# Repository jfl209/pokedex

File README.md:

# Pokédex

A software revival of the 1999 Tiger Electronics Pokémon Pokédex, running on a Raspberry Pi Zero 2 W with a 240×240 Adafruit TFT (ST7789) replacing the original LCD.

| | | |
|---|---|---|
|  |  |  |
| Original device (front) | Inside — keyboard + LiPo | Original PCB removed |

## Hardware

| Component | Part |
|-----------|------|
| Shell | Tiger Electronics Pokédex (1999) |
| SBC | Raspberry Pi Zero 1.1 W / Zero 2 W |
| Display | Adafruit 1.3" 240×240 TFT (ST7789, SPI) |
| Keyboard | Original PCB re-routed through custom PCB; scanned by ATtiny1614 over USB HID |
| Audio | Original speaker wired to Pi audio output |

### Custom PCB

The [`hardware/`](hardware/) directory contains the KiCad schematic and PCB layout for the interface board that sits between the Pi and the original Pokédex keyboard membrane.

| File | Description |
|------|-------------|
| `pi-zero-mainboard.kicad_sch` | Schematic |
| `pi-zero-mainboard.kicad_pcb` | PCB layout |
| `pi-zero-mainboard.kicad_pro` | KiCad project file |

## Software architecture

```
main.py                 Entry point — game loop
config.py               Constants: resolution, scale factor, palette, paths

data/
  fetch.py              One-time setup: pulls Gen-1 data from PokéAPI → SQLite + assets
  db.py                 SQLite query layer (Pokemon dataclass, get_all/get_by_id/search)

engine/
  display.py            Pygame surface abstraction (scaled window on dev, /dev/fb0 on Pi)
  input.py              Keyboard → Button enum (UP/DOWN/A/B/START/SELECT)
  sound.py              Pokémon cry playback via pygame.mixer

screens/
  base.py               Screen ABC: update(state) → Screen | None, draw(surface)
  home.py               Title / splash screen
  browse.py             Scrollable list of all 151 Pokémon
  detail.py             3-page detail view: info · stats · description
```

The display runs natively at 240×240. On a development machine it auto-scales 3× (720×720 window) so you can work without the physical hardware.

## Setup

### Dependencies

Requires Python 3.11–3.13 (pygame has no wheel for 3.14 yet).

```bash
python3.13 -m venv .venv
source .venv/bin/activate
pip install -r requirements.txt
```

### Fetch Pokémon data

Downloads sprites, cries, and stats for all 151 Gen-1 Pokémon from [PokéAPI](https://pokeapi.co). Takes ~10 minutes (rate-limited out of courtesy to the free API).

```bash
python -m data.fetch
```

### Run (development — Mac/Linux desktop)

```bash
python main.py
```

### Run (Raspberry Pi)

Install Pi-specific dependencies once:

```bash
sudo apt install python3-numpy python3-evdev -y
pip install spidev RPi.GPIO
```

Enable SPI in `/boot/firmware/config.txt` (Bookworm) or `/boot/config.txt` (Bullseye):

```ini
dtparam=spi=on
```

Then launch:

```bash
python3 main.py
```

The display driver auto-detects: ST7789 direct SPI → kmsdrm (HDMI) → offscreen.
FPS is auto-tuned: 20fps on Pi Zero 1.1 W (armv6l), 30fps everywhere else.

## Controls

| Physical key | Dev key | Action |
|---|---|---|
| D-pad up/down | `↑` `↓` | Navigate list; prev/next Pokémon in detail |
| D-pad left/right | `←` `→` | Flip detail pages |
| A | `Enter` or `Z` | Select / next page |
| B | `Backspace` or `X` | Back |
| START | `Escape` | Return to home |

## Detail pages

Each Pokémon detail view has three swipeable pages:

1. **Info** — sprite, type badges, category, height, weight
2. **Stats** — HP / ATK / DEF / SPD / SPA / SPD bars (colour-coded)
3. **Description** — original Red/Blue Pokédex flavour text

## Project status

- [x] Core game loop (display, input, sound abstractions)
- [x] PokéAPI data fetch + SQLite storage
- [x] Home, browse, and detail screens
- [ ] Search / filter screen
- [ ] Quiz mode (silhouette / cry identification)
- [ ] Battle simulation
- [ ] ATtiny1614 firmware (keyboard scanner)
- [ ] Pi OS image + auto-start service

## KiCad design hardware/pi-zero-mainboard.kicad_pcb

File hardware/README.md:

# Pi Zero 2 W Mainboard — KiCad Project

## Overview

Custom PCB that the Pi Zero 2 W plugs into via GPIO header. Integrates:
- USB-C charging (MCP73871 power-path manager)
- 3.7V→5.2V boost (TPS61090)
- Soft-latch power control via TPS61090 EN pin
- 1.54" 240×240 TFT display connector (ST7789, SPI)
- MAX98357A I2S DAC + Class D amp with speaker connector
- ATtiny1614 keyboard controller (on-board, SOIC-14)
- 48 switches + 48 diodes (charlieplex matrix, directly on PCB)

Board dimensions: 76 × 114 mm (3" × 4.5"), 2-layer, 1.6mm thickness.

## Power Architecture

Based on the **Adafruit PowerBoost 1000C** (open-source hardware).
Copy the MCP73871 and TPS61090 subcircuits with all component values
from the PowerBoost 1000C schematic (Eagle files on GitHub).

### Changes from PowerBoost 1000C

| What | PowerBoost 1000C | This board |
|------|-----------------|------------|
| USB input | Micro-USB | USB-C with 5.1kΩ CC pulldowns |
| USB output | USB-A jack + iOS resistors | Removed (not needed) |
| Power LED | Blue LED on 5V output | Removed (saves ~5mA) |
| EN pin | Pulled high to VS (always on) | Driven by POWER_CTRL net (soft-latch) |
| Low battery | Red LED on LBO | Keep LED, optionally route to Pi GPIO |

### Soft-Latch Power Control

No P-FET or external latch circuit needed! The TPS61090's EN pin does it all:

- R5 (100kΩ) pulls EN to GND → boost OFF by default
- ATtiny1614 PB3 drives POWER_CTRL HIGH → boost ON (Pi boots)
- Pi GPIO 26 also drives POWER_CTRL HIGH (wired-OR with ATtiny)
- Pi shutdown releases GPIO 26, ATtiny releases PB3 → EN goes LOW → power off
- Quiescent draw in off state: ~20µA (TPS61090 disabled)

### ATtiny1614 Always-On Power

The ATtiny1614 (on the keyboard PCB) connects directly to VLIPO (raw battery)
through J1 pin 1. It draws ~1µA in power-down sleep mode, waking on
pin-change interrupt when the ON key is pressed.

## Net Names

| Net | Description | Source |
|-----|-------------|--------|
| VBUS | USB-C 5V input | J6 USB-C connector |
| VLIPO | Raw battery (3.0–4.2V) | J2 LiPo JST connector |
| VBAT_OUT | MCP73871 OUT (load-shared) | U1 pin 19 |
| 5V_BOOST | TPS61090 output (5.2V) | U2 pin 1 → Pi pin 2 |
| POWER_CTRL | Soft-latch enable | ATtiny PB3 + Pi GPIO 26 → U2 EN |
| +3V3 | Pi 3.3V rail (from Pi's regulator) | Pi pin 1 |
| SDA | I2C data | Pi GPIO 2 (pin 3) ↔ ATtiny PA1 |
| SCL | I2C clock | Pi GPIO 3 (pin 5) ↔ ATtiny PA2 |

## GPIO Assignment (Pi Zero 2 W)

| GPIO | Pin | Function | Peripheral |
|------|-----|----------|-----------|
| 2 | 3 | I2C SDA | Keyboard (ATtiny1614) |
| 3 | 5 | I2C SCL | Keyboard (ATtiny1614) |
| 4 | 7 | SD_MODE | MAX98357A shutdown |
| 8 | 24 | SPI0 CE0 | Display TFT CS |
| 10 | 19 | SPI0 MOSI | Display data |
| 11 | 23 | SPI0 SCLK | Display clock |
| 18 | 12 | I2S BCLK | MAX98357A bit clock |
| 19 | 35 | I2S LRCLK | MAX98357A word clock |
| 21 | 40 | I2S DIN | MAX98357A data in |
| 25 | 22 | DC | Display data/command |
| 26 | 37 | KEEP_ALIVE | POWER_CTRL (soft-latch) |

## Connector Pinouts

### J1 — Keyboard (5-pin, to keyboard PCB)
| Pin | Signal | Notes |
|-----|--------|-------|
| 1 | VLIPO | ATtiny always-on power (3.0–4.2V) |
| 2 | SDA | I2C data (Pi has 1.8kΩ pull-up) |
| 3 | SCL | I2C clock (Pi has 1.8kΩ pull-up) |
| 4 | GND | Ground |
| 5 | POWER_CTRL | ATtiny PB3 output to TPS61090 EN |

### J2 — LiPo Battery (JST-PH 2-pin)
| Pin | Signal |
|-----|--------|
| 1 | VLIPO (+) |
| 2 | GND (−) |

### J4 — Display (7-pin header)
| Pin | Signal | Pi GPIO |
|-----|--------|---------|
| 1 | 3.3V | Pin 1 |
| 2 | GND | Pin 6 |
| 3 | SPI_SCLK | GPIO 11 |
| 4 | SPI_MOSI | GPIO 10 |
| 5 | SPI_CE0 | GPIO 8 |
| 6 | DC | GPIO 25 |
| 7 | RST | GPIO 24 (or tie to 3.3V via RC) |

### J5 — Speaker (JST-PH 2-pin)
| Pin | Signal |
|-----|--------|
| 1 | OUTP |
| 2 | OUTN |

## BOM (Key Components)

| Ref | Part | Package | Value/Part # | Notes |
|-----|------|---------|-------------|-------|
| U1 | MCP73871-2CCI/ML | QFN-20 4×4mm | — | Copy from PowerBoost |
| U2 | TPS61090RSAR | PVQFN-16 | — | Copy from PowerBoost |
| U3 | MAX98357AETE | TQFN-16 3×3mm | — | I2S DAC + amp |
| J6 | USB-C receptacle | GCT USB4085 | — | Mid-mount |
| J3 | 2×20 female header | 2.54mm pitch | — | For Pi Zero GPIO |
| J1 | 1×5 pin header | 2.54mm pitch | — | Keyboard cable |
| J2 | JST-PH 2-pin | S2B-PH-K | — | LiPo battery |
| J4 | 1×7 pin header | 2.54mm pitch | — | Display module |
| J5 | JST-PH 2-pin | S2B-PH-K | — | Speaker |
| L1 | Inductor | 5×5mm | 6.8µH | TDK VLC5045 or similar |
| R1,R2 | Resistor | 0402 | 5.1kΩ | USB-C CC pulldowns |
| R5 | Resistor | 0402 | 100kΩ | EN pull-down (soft-latch) |
| — | (PowerBoost passives) | 0402/0805 | Various | Copy values from PB1000C |

## Getting Started

1. Open `pi-zero-mainboard.kicad_pro` in KiCad 8
2. The schematic has all symbols defined inline (no external libs needed)
3. Download the [Adafruit PowerBoost 1000C Eagle files](https://github.com/adafruit/Adafruit-PowerBoost-1000C)
4. Reference the Eagle schematic for exact MCP73871 and TPS61090 passive values
5. Add the PowerBoost passives to this schematic around U1 and U2
6. Assign footprints (most are pre-assigned, verify against KiCad 8 libraries)
7. Run ERC, then transfer to PCB editor
8. Place components per the layout diagram, route traces

## PCB Layout Notes

- **Power traces**: Use 0.5mm minimum for VLIPO, VBAT_OUT, 5V_BOOST
- **TPS61090 layout**: Keep L1, input cap, and output cap as close as possible
  to the IC. Follow TI's layout guidelines in the TPS61090 datasheet.
- **Ground plane**: Pour copper on both layers, stitched with vias
- **USB-C**: Edge-mount at bottom of board
- **Battery**: JST connector on bottom edge, pouch cell sits under the PCB
- **Display/audio headers**: Right side of board for cable routing

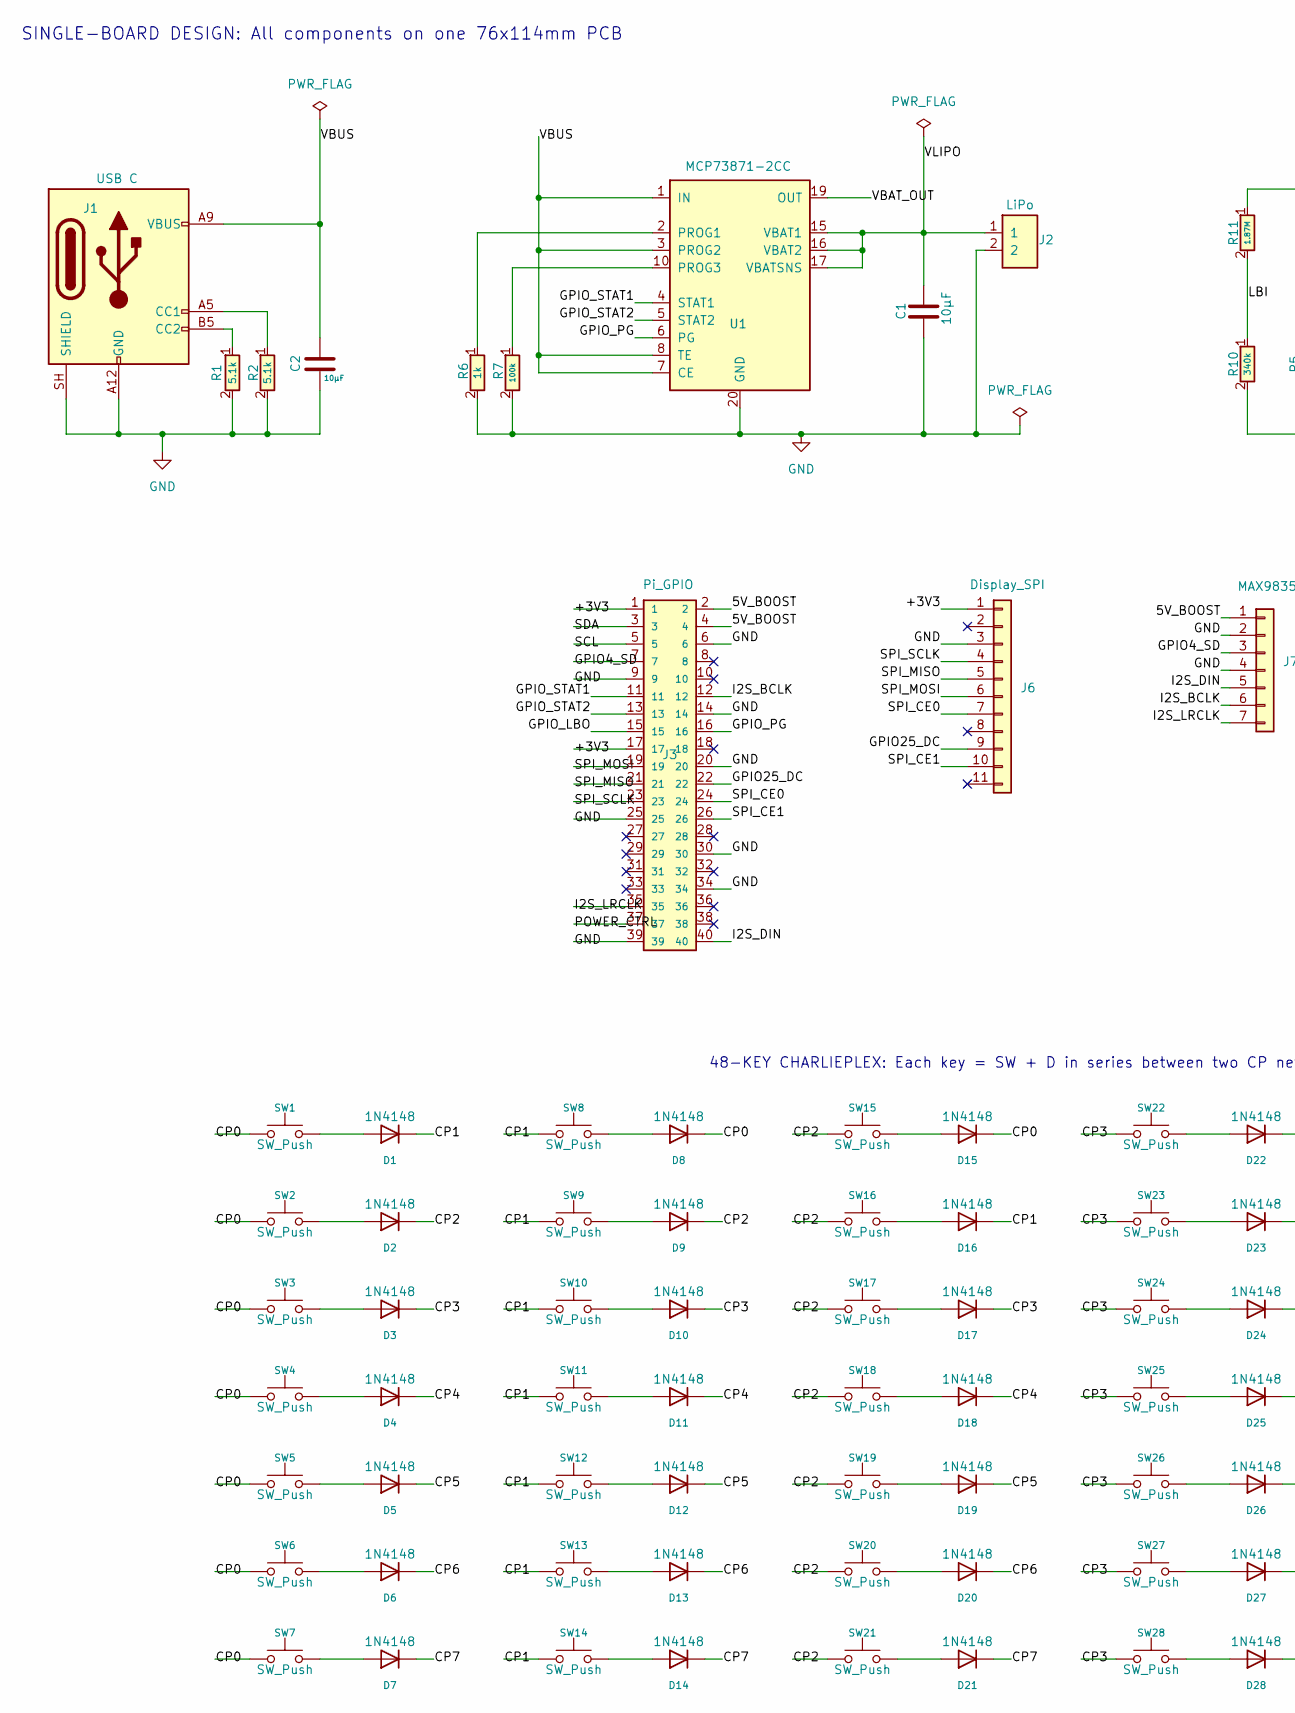
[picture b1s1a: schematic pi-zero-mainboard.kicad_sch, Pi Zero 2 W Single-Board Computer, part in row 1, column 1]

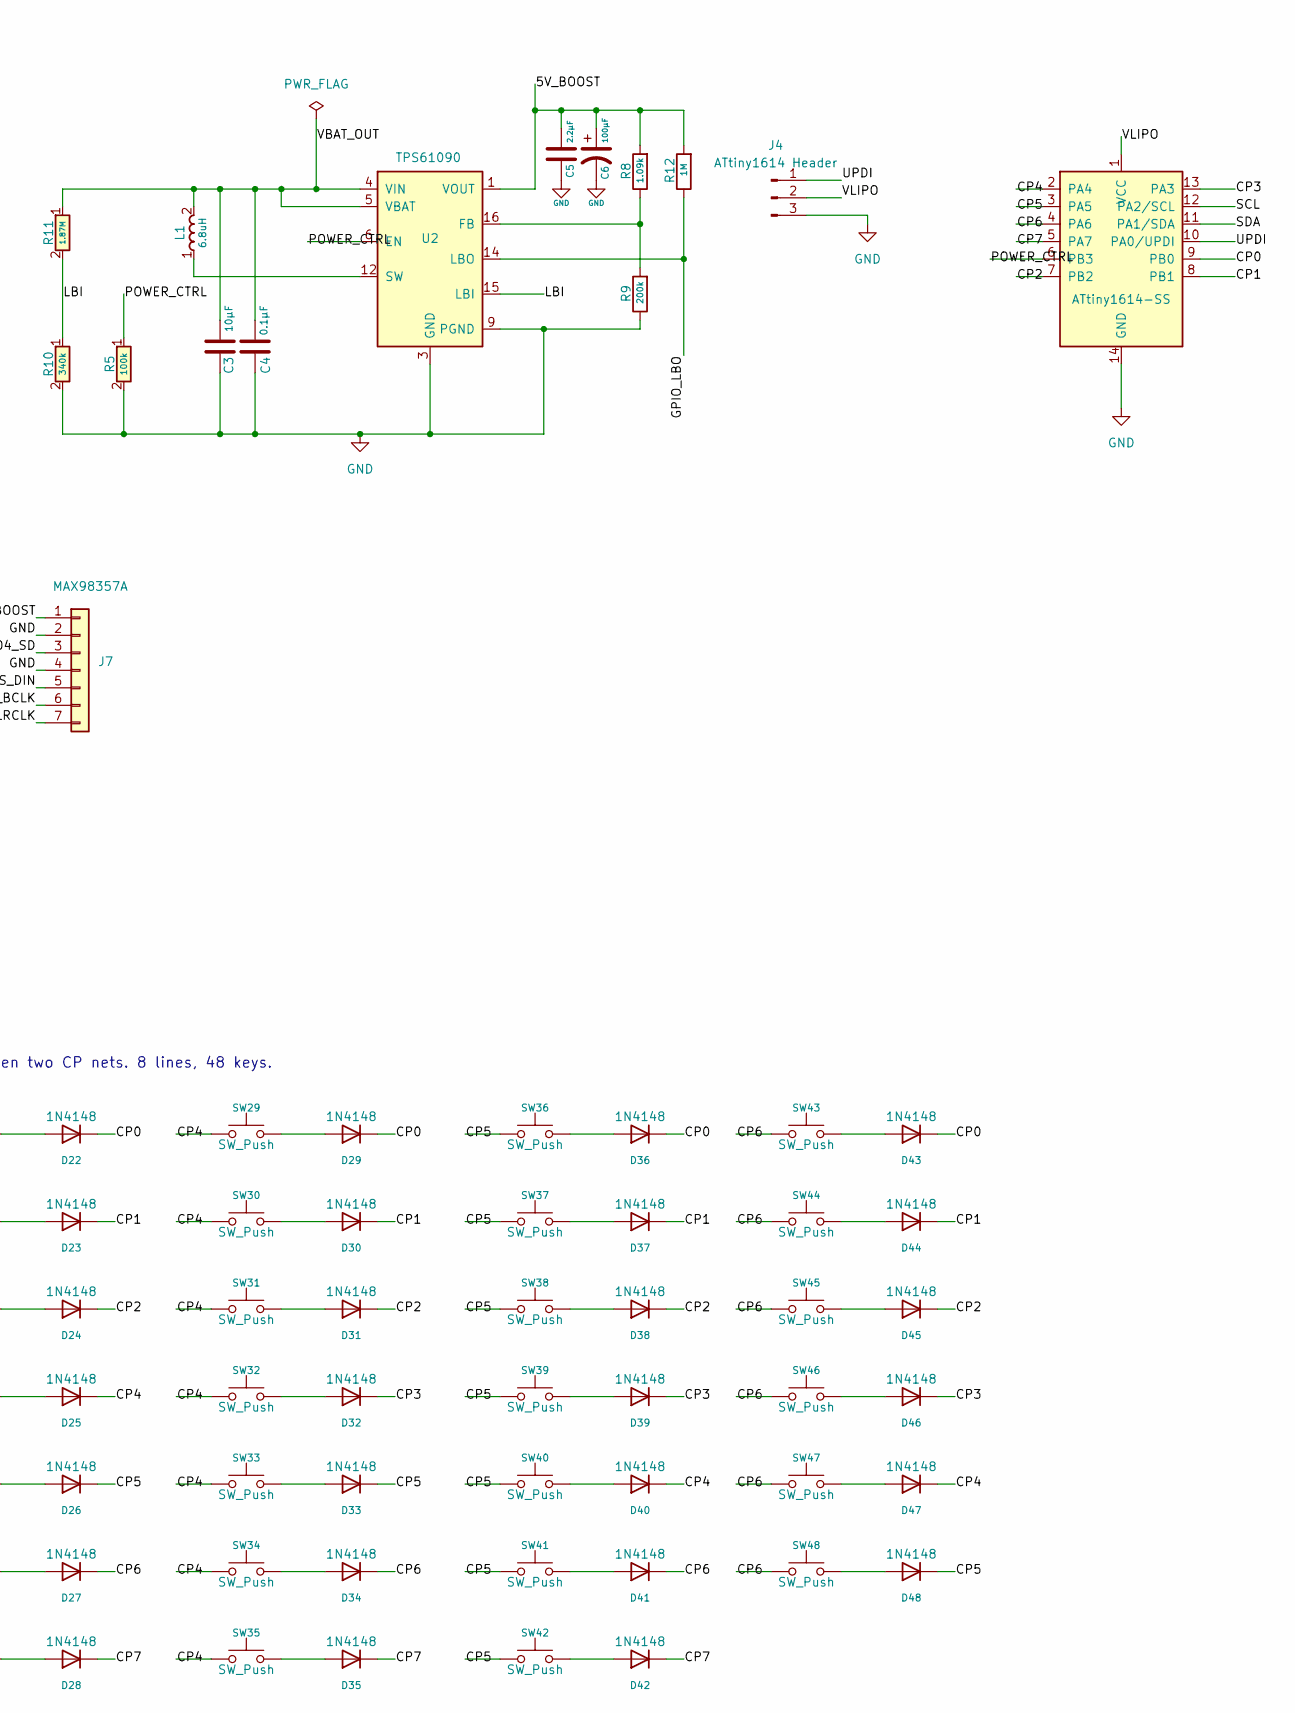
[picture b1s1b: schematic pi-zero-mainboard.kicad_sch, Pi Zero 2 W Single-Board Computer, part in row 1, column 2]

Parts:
C1, C2, C3: 10µF; C_0603_1608Metric
C4: 0.1µF; C_0603_1608Metric
C5: 2.2µF; C_0603_1608Metric
C6: 100µF; C_0603_1608Metric
D1, D2, D3, D4, D5, D6, D7, D8, D9, D10, D11, D12, D13, D14, D15, D16, D17, D18, D19, D20, D21, D22, D23, D24, D25, D26, D27, D28, D29, D30, D31, D32, D33, D34, D35, D36, D37, D38, D39, D40, D41, D42, D43, D44, D45, D46, D47, D48: 1N4148; D_SOD-323_HandSoldering
J1: USB C; USB_C_Receptacle_GCT_USB4085
J2: LiPo; JST_PH_S2B-PH-K_1x02_P2.00mm_Horizontal
J3: Pi_GPIO; PinSocket_2x20_P2.54mm_Vertical_SMD
J4: ATtiny1614 Header; PinHeader_1x03_P2.54mm_Horizontal
J6: Display_SPI; PinSocket_1x11_P2.54mm_Vertical_SMD_Pin1Right
J7: MAX98357A; PinSocket_1x07_P2.54mm_Vertical_SMD_Pin1Left
L1: 6.8uH; L_Taiyo-Yuden_NR-50xx_HandSoldering
R1: 5.1k; R_0603_1608Metric_Pad0.98x0.95mm_HandSolder
R2: 5.1k; R_0603_1608Metric
R5, R7: 100k; R_0603_1608Metric
R6: 1k; R_0603_1608Metric
R8: 1.09k; R_0603_1608Metric
R9: 200k; R_0603_1608Metric
R10: 340k; R_0603_1608Metric
R11: 1.87M; R_0603_1608Metric
R12: 1M; R_0603_1608Metric
SW1, SW2, SW3, SW4, SW5, SW6, SW7, SW8, SW9, SW10, SW11, SW12, SW13, SW14, SW15, SW16, SW17, SW18, SW19, SW20, SW21, SW22, SW23, SW24, SW25, SW26, SW27, SW28, SW29, SW30, SW31, SW32, SW33, SW34, SW35, SW36, SW37, SW38, SW39, SW40, SW41: SW_Push; conductive pad
SW42, SW43, SW44, SW45, SW46: SW_Push; rectangular conductive pad - 8x3
SW47: SW_Push; rectangular conductive pad - 18x5
SW48: SW_Push; rectangular conductive pad - 25x3
U1: MCP73871-2CC; QFN-20-1EP_4x4mm_P0.5mm_EP2.5x2.5mm
U2: TPS61090; QFN-16-1EP_3x3mm_P0.5mm_EP1.7x1.7mm
U4: ATtiny1614-SS; SOIC-14_3.9x8.7mm_P1.27mm

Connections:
/5V_BOOST: C5.1, C6.1, J3.2, J3.4, J7.1, R8.2, R12.2, U2.1 (VOUT)
/+3V3: J3.1, J3.17, J6.1
/CP0: D8.1 (K), D15.1 (K), D22.1 (K), D29.1 (K), D36.1 (K), D43.1 (K), SW1.1, SW2.1, SW3.1, SW4.1, SW5.1, SW6.1, SW7.1, U4.9 (PB0)
/CP1: D1.1 (K), D16.1 (K), D23.1 (K), D30.1 (K), D37.1 (K), D44.1 (K), SW8.1, SW9.1, SW10.1, SW11.1, SW12.1, SW13.1, SW14.1, U4.8 (PB1)
/CP2: D2.1 (K), D9.1 (K), D24.1 (K), D31.1 (K), D38.1 (K), D45.1 (K), SW15.1, SW16.1, SW17.1, SW18.1, SW19.1, SW20.1, SW21.1, U4.7 (PB2)
/CP3: D3.1 (K), D10.1 (K), D17.1 (K), D32.1 (K), D39.1 (K), D46.1 (K), SW22.1, SW23.1, SW24.1, SW25.1, SW26.1, SW27.1, SW28.1, U4.13 (PA3)
/CP4: D4.1 (K), D11.1 (K), D18.1 (K), D25.1 (K), D40.1 (K), D47.1 (K), SW29.1, SW30.1, SW31.1, SW32.1, SW33.1, SW34.1, SW35.1, U4.2 (PA4)
/CP5: D5.1 (K), D12.1 (K), D19.1 (K), D26.1 (K), D33.1 (K), D48.1 (K), SW36.1, SW37.1, SW38.1, SW39.1, SW40.1, SW41.1, SW42.1, U4.3 (PA5)
/CP6: D6.1 (K), D13.1 (K), D20.1 (K), D27.1 (K), D34.1 (K), D41.1 (K), SW43.1, SW44.1, SW45.1, SW46.1, SW47.1, SW48.1, U4.4 (PA6)
/CP7: D7.1 (K), D14.1 (K), D21.1 (K), D28.1 (K), D35.1 (K), D42.1 (K), U4.5 (PA7)
/GPIO4_SD: J3.7, J7.3
/GPIO25_DC: J3.22, J6.9
/GPIO_LBO: J3.15, R12.1, U2.14 (LBO)
/GPIO_PG: J3.16, U1.6 (PG)
/GPIO_STAT1: J3.11, U1.4 (STAT1)
/GPIO_STAT2: J3.13, U1.5 (STAT2)
/I2S_BCLK: J3.12, J7.6
/I2S_DIN: J3.40, J7.5
/I2S_LRCLK: J3.35, J7.7
/LBI: R10.1, R11.2, U2.15 (LBI)
/POWER_CTRL: J3.37, R5.1, U2.6 (EN), U4.6 (PB3)
/SCL: J3.5, U4.12 (PA2/SCL)
/SDA: J3.3, U4.11 (PA1/SDA)
/SPI_CE0: J3.24, J6.7
/SPI_CE1: J3.26, J6.10
/SPI_MISO: J3.21, J6.5
/SPI_MOSI: J3.19, J6.6
/SPI_SCLK: J3.23, J6.4
/UPDI: J4.1, U4.10 (PA0/UPDI)
/VBAT_OUT: C3.1, C4.1, L1.2, R11.1, U1.19 (OUT), U2.4 (VIN), U2.5 (VBAT)
/VBUS: C2.1, J1.A9 (VBUS), J1.B9 (VBUS), U1.1 (IN), U1.3 (PROG2), U1.7 (CE), U1.8 (TE)
/VLIPO: C1.1, J2.1, J4.2, U1.15 (VBAT1), U1.16 (VBAT2), U1.17 (VBATSNS), U4.1 (VCC)
GND: C1.2, C2.2, C3.2, C4.2, C5.2, C6.2, J1.A12 (GND), J1.B12 (GND), J1.SH (SHIELD), J2.2, J3.6, J3.9, J3.14, J3.20, J3.25, J3.30, J3.34, J3.39, J4.3, J6.3, J7.2, J7.4, R1.2, R2.2, R5.2, R6.2, R7.2, R9.1, R10.2, U1.20 (GND), U2.3 (GND), U2.9 (PGND), U4.14 (GND)
unnamed: D1.2 (A), SW1.2
unnamed: D2.2 (A), SW2.2
unnamed: D3.2 (A), SW3.2
unnamed: D4.2 (A), SW4.2
unnamed: D5.2 (A), SW5.2
unnamed: D6.2 (A), SW6.2
unnamed: D7.2 (A), SW7.2
unnamed: D8.2 (A), SW8.2
unnamed: D9.2 (A), SW9.2
unnamed: D10.2 (A), SW10.2
unnamed: D11.2 (A), SW11.2
unnamed: D12.2 (A), SW12.2
unnamed: D13.2 (A), SW13.2
unnamed: D14.2 (A), SW14.2
unnamed: D15.2 (A), SW15.2
unnamed: D16.2 (A), SW16.2
unnamed: D17.2 (A), SW17.2
unnamed: D18.2 (A), SW18.2
unnamed: D19.2 (A), SW19.2
unnamed: D20.2 (A), SW20.2
unnamed: D21.2 (A), SW21.2
unnamed: D22.2 (A), SW22.2
unnamed: D23.2 (A), SW23.2
unnamed: D24.2 (A), SW24.2
unnamed: D25.2 (A), SW25.2
unnamed: D26.2 (A), SW26.2
unnamed: D27.2 (A), SW27.2
unnamed: D28.2 (A), SW28.2
unnamed: D29.2 (A), SW29.2
unnamed: D30.2 (A), SW30.2
unnamed: D31.2 (A), SW31.2
unnamed: D32.2 (A), SW32.2
unnamed: D33.2 (A), SW33.2
unnamed: D34.2 (A), SW34.2
unnamed: D35.2 (A), SW35.2
unnamed: D36.2 (A), SW36.2
unnamed: D37.2 (A), SW37.2
unnamed: D38.2 (A), SW38.2
unnamed: D39.2 (A), SW39.2
unnamed: D40.2 (A), SW40.2
unnamed: D41.2 (A), SW41.2
unnamed: D42.2 (A), SW42.2
unnamed: D43.2 (A), SW43.2
unnamed: D44.2 (A), SW44.2
unnamed: D45.2 (A), SW45.2
unnamed: D46.2 (A), SW46.2
unnamed: D47.2 (A), SW47.2
unnamed: D48.2 (A), SW48.2
unnamed: J1.A5 (CC1), R2.1
unnamed: J1.B5 (CC2), R1.1
unnamed: R6.1, U1.2 (PROG1)
unnamed: R7.1, U1.10 (PROG3)
unnamed: R8.1, R9.2, U2.16 (FB)
unnamed: L1.1, U2.12 (SW)

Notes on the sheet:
SINGLE-BOARD DESIGN: All components on one 76x114mm PCB
48-KEY CHARLIEPLEX: Each key = SW + D in series between two CP nets. 8 lines, 48 keys.

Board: 2 copper layers, 122 parts (0 on the bottom side), 86 nets, no tracks yet.
